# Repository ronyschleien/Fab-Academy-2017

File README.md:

# Fab-Academy-2017
All the files of my exercises

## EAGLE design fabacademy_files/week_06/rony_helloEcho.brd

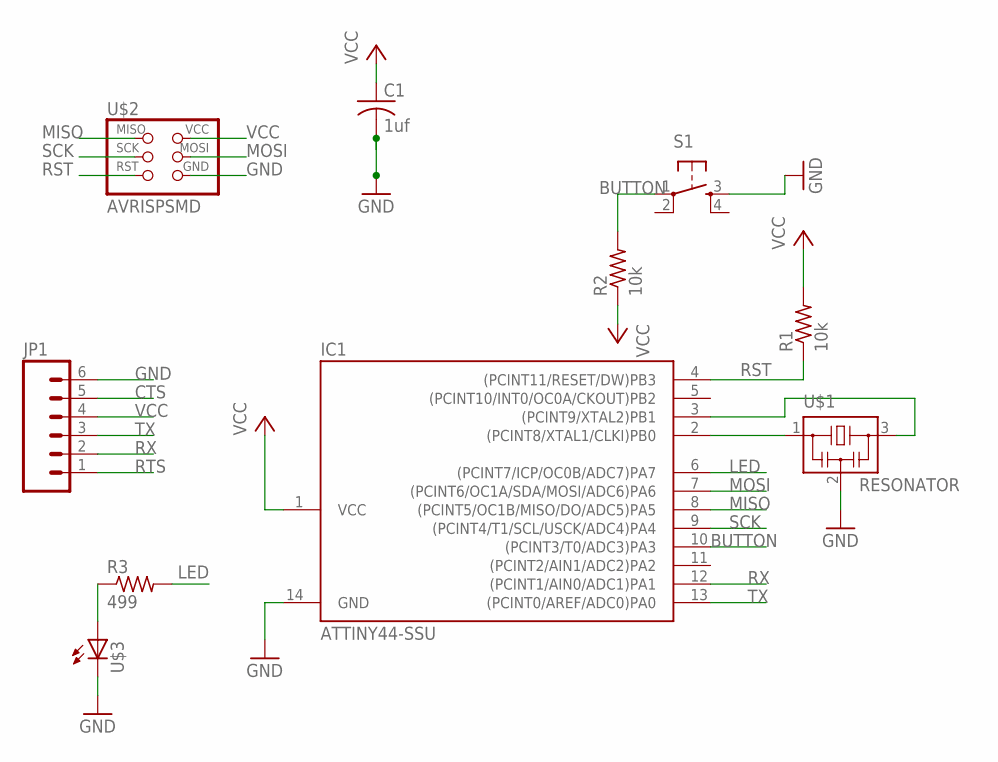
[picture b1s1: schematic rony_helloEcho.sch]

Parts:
C1: 1uf; C1206
IC1: ATTINY44-SSU; SOIC14
JP1: M06SMD; 1X06-SMD
R1, R2: 10k; R1206
R3: 499; R1206FAB
S1: 6MM_SWITCH6MM_SWITCH; 6MM_SWITCH
U$1: RESONATOR; EFOBM
U$2: AVRISPSMD; 2X03SMD
U$3: LED1206; 1206

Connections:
BUTTON: IC1.10 ((PCINT3/T0/ADC3)PA3), R2.2, S1.1
CTS: JP1.5
GND: C1.2, IC1.14 (GND), JP1.6, S1.3 (S), U$1.2, U$2.6 (GND), U$3.2 (C)
LED: IC1.6 ((PCINT7/ICP/OC0B/ADC7)PA7), R3.2
MISO: IC1.8 ((PCINT5/OC1B/MISO/DO/ADC5)PA5), U$2.1 (MISO)
MOSI: IC1.7 ((PCINT6/OC1A/SDA/MOSI/ADC6)PA6), U$2.4 (MOSI)
unnamed: IC1.2 ((PCINT8/XTAL1/CLKI)PB0), U$1.1
unnamed: IC1.3 ((PCINT9/XTAL2)PB1), U$1.3
unnamed: R3.1, U$3.1 (A)
RST: IC1.4 ((PCINT11/RESET/DW)PB3), R1.1, U$2.5 (RST)
RTS: JP1.1
RX: IC1.12 ((PCINT1/AIN0/ADC1)PA1), JP1.2
SCK: IC1.9 ((PCINT4/T1/SCL/USCK/ADC4)PA4), U$2.3 (SCK)
TX: IC1.13 ((PCINT0/AREF/ADC0)PA0), JP1.3
VCC: C1.1, IC1.1 (VCC), JP1.4, R1.2, R2.1, U$2.2 (VCC)

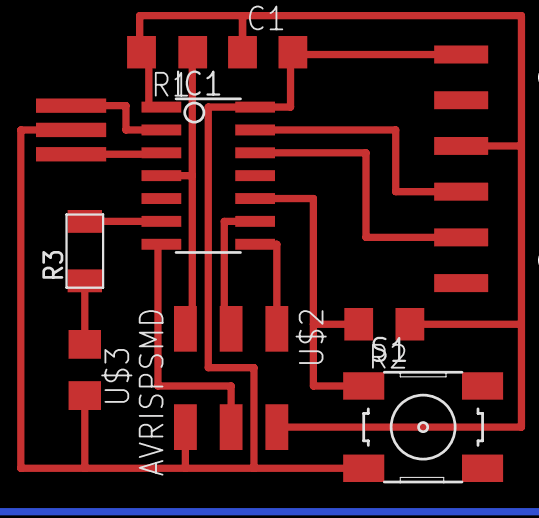
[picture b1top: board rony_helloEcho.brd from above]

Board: 1 copper layer, 10 parts (0 on the bottom side), 13 nets.

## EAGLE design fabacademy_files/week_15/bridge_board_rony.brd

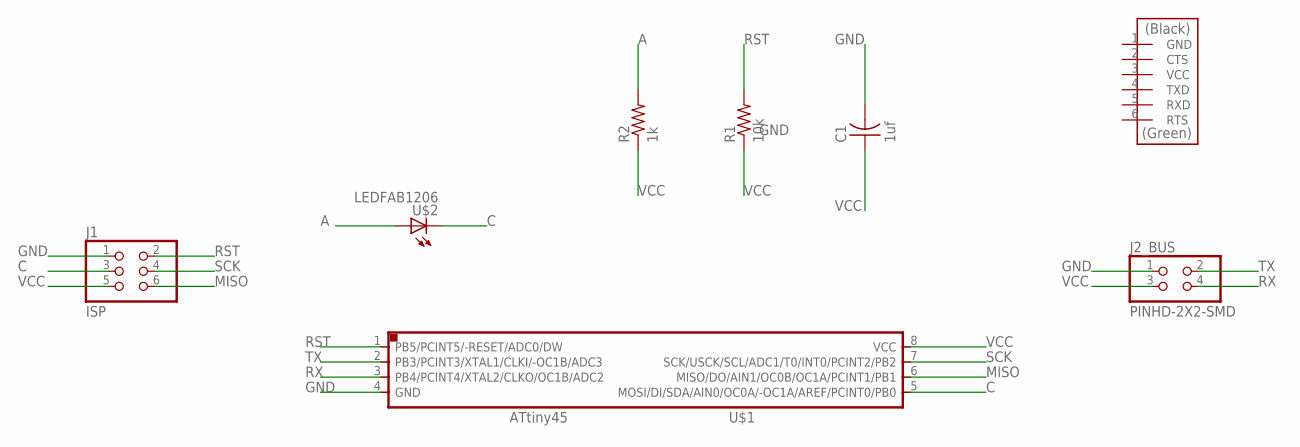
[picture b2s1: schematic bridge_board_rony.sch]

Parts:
C1: 1uf; C1206FAB
J1: ISP; 2X03SMD
J2_BUS: PINHD-2X2-SMD; 2X02SMD
R1: 10k; R1206FAB
R2: 1k; R1206FAB
U$1: ATTINY45SI; SOIC8
U$2: LEDFAB1206; LED1206FAB
U$3: FTDI-SMD-HEADER; 1X06SMD

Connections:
A: R2.2, U$2.1 (A)
C: J1.3, U$1.5 (MOSI/DI/SDA/AIN0/OC0A/-OC1A/AREF/PCINT0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), U$2.2 (C)
GND: C1.2, J1.1, J2_BUS.1, U$1.4 (GND)
MISO: J1.6, U$1.6 (MISO/DO/AIN1/OC0B/OC1A/PCINT1/PB1)
RST: J1.2, R1.2, U$1.1 (PB5/PCINT5/-RESET/ADC0/DW)
RX: J2_BUS.4, U$1.3 (PB4/PCINT4/XTAL2/CLKO/OC1B/ADC2)
SCK: J1.4, U$1.7 (SCK/USCK/SCL/ADC1/T0/INT0/PCINT2/PB2)
TX: J2_BUS.2, U$1.2 (PB3/PCINT3/XTAL1/CLKI/-OC1B/ADC3)
VCC: C1.1, J1.5, J2_BUS.3, R1.1, R2.1, U$1.8 (VCC)

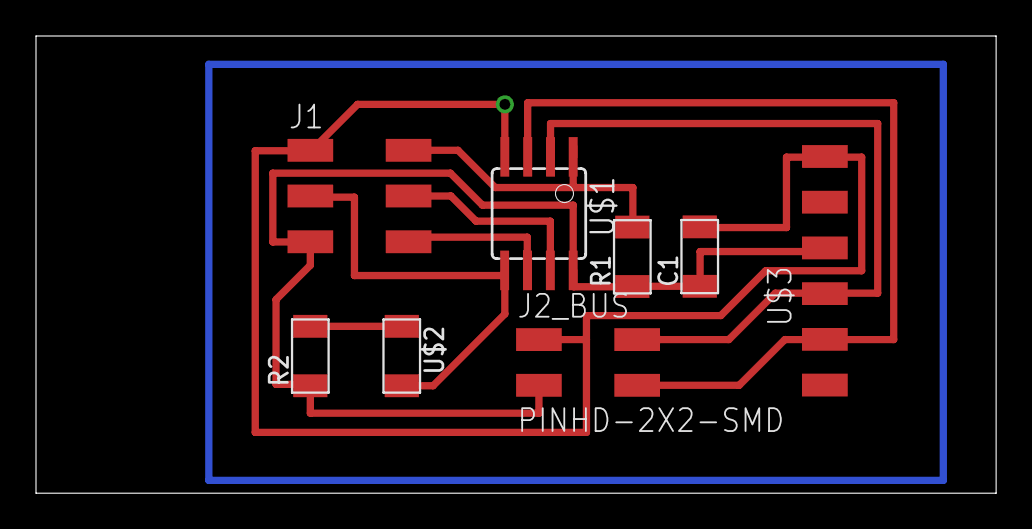
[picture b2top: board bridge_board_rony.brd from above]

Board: 2 copper layers, 53.3 x 25.4 mm, 8 parts (0 on the bottom side), 9 nets.

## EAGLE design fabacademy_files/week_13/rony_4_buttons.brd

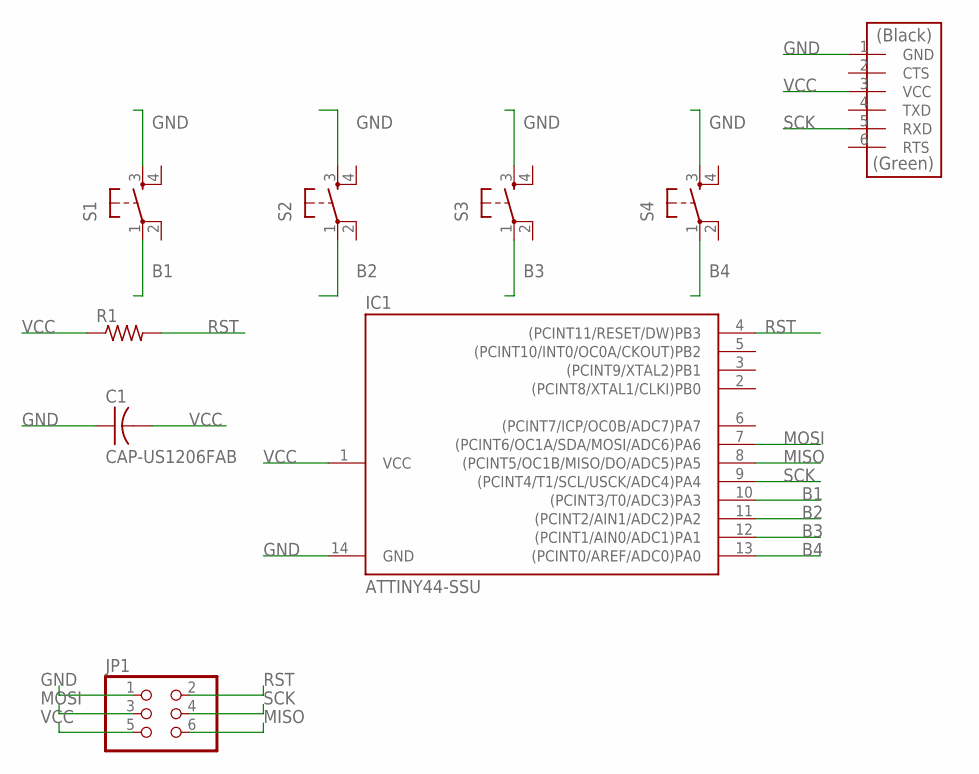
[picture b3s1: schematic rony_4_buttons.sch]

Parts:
C1: CAP-US1206FAB; C1206FAB
IC1: ATTINY44-SSU; SOIC14
JP1: PINHD-2X3-SMD; 2X03SMD
R1: RES-US1206FAB; R1206FAB
S1, S2, S3, S4: 6MM_SWITCH6MM_SWITCH; 6MM_SWITCH
U$1: FTDI-SMD-HEADER; 1X06SMD

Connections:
B1: IC1.10 ((PCINT3/T0/ADC3)PA3), S1.1
B2: IC1.11 ((PCINT2/AIN1/ADC2)PA2), S2.1
B3: IC1.12 ((PCINT1/AIN0/ADC1)PA1), S3.1
B4: IC1.13 ((PCINT0/AREF/ADC0)PA0), S4.1
GND: C1.1, IC1.14 (GND), JP1.1, S1.3 (S), S2.3 (S), S3.3 (S), S4.3 (S), U$1.1 (GND)
MISO: IC1.8 ((PCINT5/OC1B/MISO/DO/ADC5)PA5), JP1.6
MOSI: IC1.7 ((PCINT6/OC1A/SDA/MOSI/ADC6)PA6), JP1.3
RST: IC1.4 ((PCINT11/RESET/DW)PB3), JP1.2, R1.2
SCK: IC1.9 ((PCINT4/T1/SCL/USCK/ADC4)PA4), JP1.4, U$1.5 (RXD)
VCC: C1.2, IC1.1 (VCC), JP1.5, R1.1, U$1.3 (VCC)

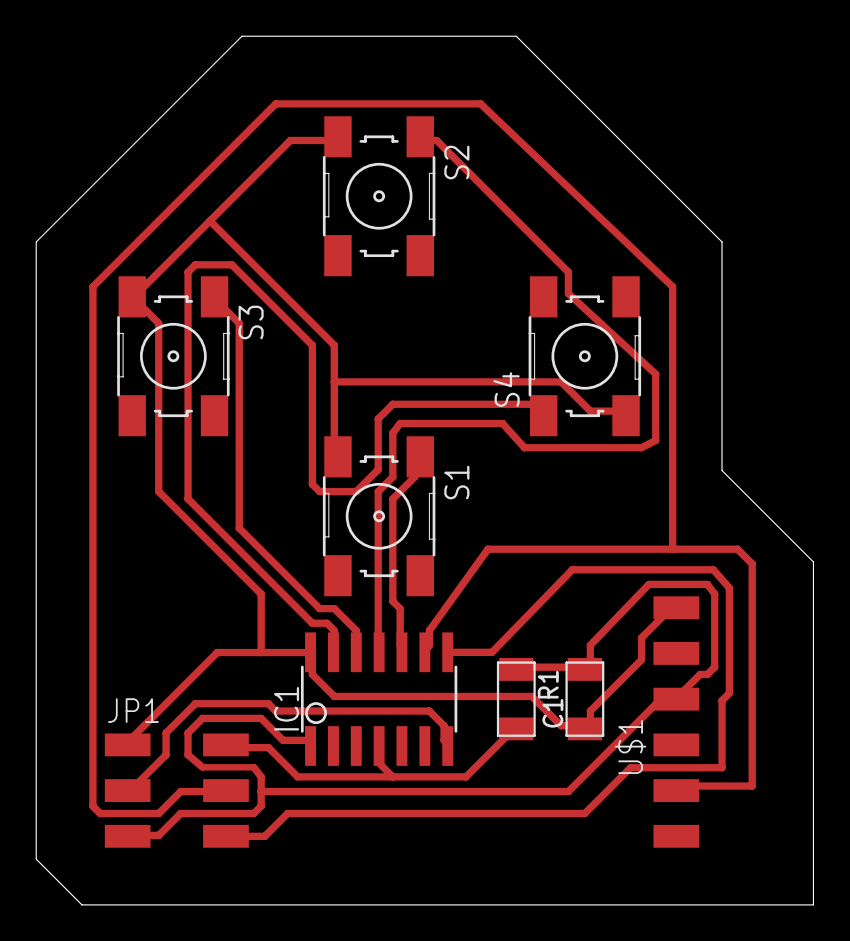
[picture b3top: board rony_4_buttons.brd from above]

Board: 2 copper layers, 43.2 x 48.3 mm, 9 parts (0 on the bottom side), 10 nets.

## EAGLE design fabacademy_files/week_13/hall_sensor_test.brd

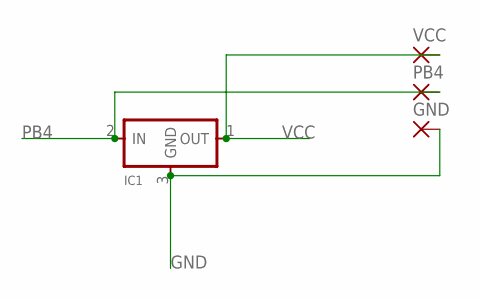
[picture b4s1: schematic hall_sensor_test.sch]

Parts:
GND: SMD2; SMD1,27-2,54
IC1: REGULATORSOT23; SOT23
PB4: SMD2; SMD1,27-2,54
VCC: SMD2; SMD1,27-2,54

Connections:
GND: GND.1, IC1.3 (GND)
PB4: IC1.2 (IN), PB4.1
VCC: IC1.1 (OUT), VCC.1

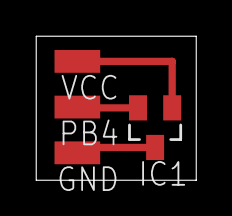
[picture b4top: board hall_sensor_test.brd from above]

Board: 2 copper layers, 8.9 x 8.0 mm, 4 parts (0 on the bottom side), 3 nets.

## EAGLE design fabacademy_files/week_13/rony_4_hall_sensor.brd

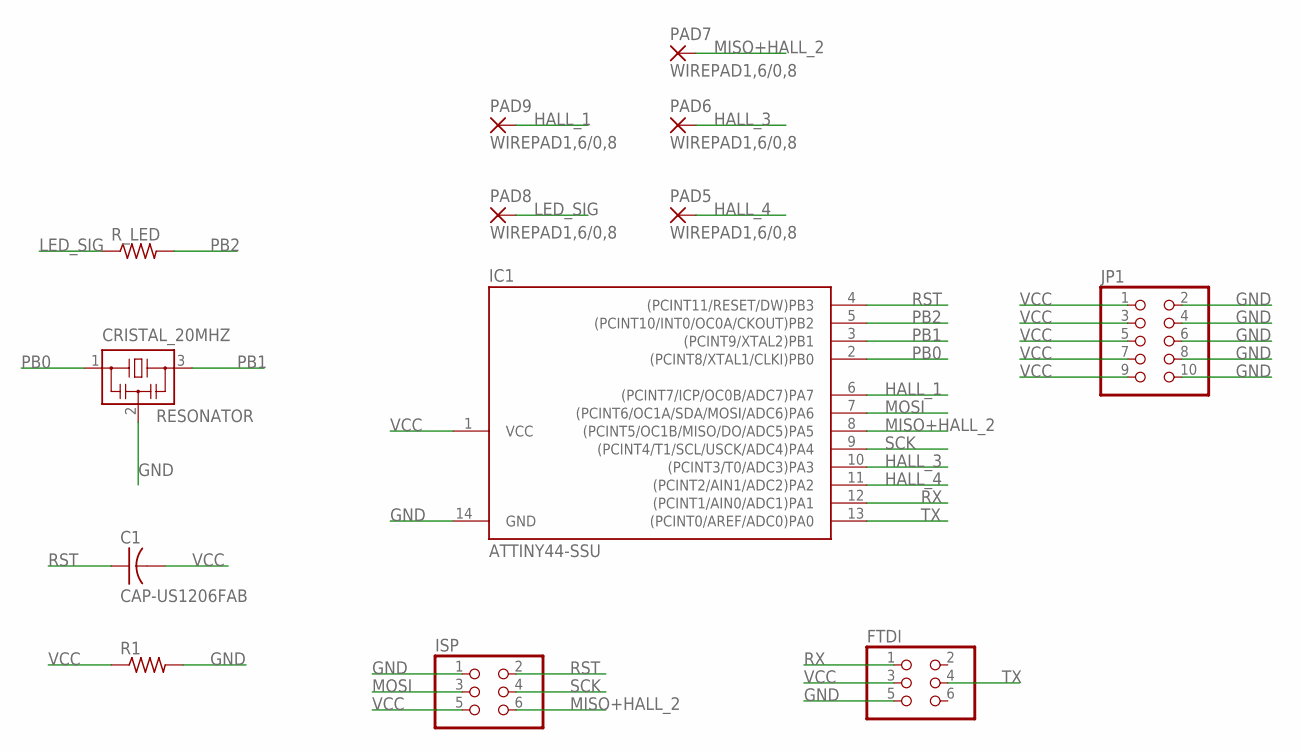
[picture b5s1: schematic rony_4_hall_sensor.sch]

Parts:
C1: CAP-US1206FAB; C1206FAB
CRISTAL_20MHZ: RESONATOR; EFOBM
FTDI: PINHD-2X3-SMD; 2X03SMD
IC1: ATTINY44-SSU; SOIC14
ISP: PINHD-2X3-SMD; 2X03SMD
JP1: PINHD-2X5; 2X05
PAD5, PAD6, PAD7, PAD8, PAD9: WIREPAD1,6/0,8; 1,6/0,8
R1: RES-US1206FAB; R1206FAB
R_LED: RES-US1206FAB; R1206FAB

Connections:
GND: CRISTAL_20MHZ.2, FTDI.5, IC1.14 (GND), ISP.1, JP1.2, JP1.4, JP1.6, JP1.8, JP1.10, R1.2
HALL_1: IC1.6 ((PCINT7/ICP/OC0B/ADC7)PA7), PAD9.1
HALL_3: IC1.10 ((PCINT3/T0/ADC3)PA3), PAD6.1
HALL_4: IC1.11 ((PCINT2/AIN1/ADC2)PA2), PAD5.1
LED_SIG: PAD8.1, R_LED.1
MISO+HALL_2: IC1.8 ((PCINT5/OC1B/MISO/DO/ADC5)PA5), ISP.6, PAD7.1
MOSI: IC1.7 ((PCINT6/OC1A/SDA/MOSI/ADC6)PA6), ISP.3
PB0: CRISTAL_20MHZ.1, IC1.2 ((PCINT8/XTAL1/CLKI)PB0)
PB1: CRISTAL_20MHZ.3, IC1.3 ((PCINT9/XTAL2)PB1)
PB2: IC1.5 ((PCINT10/INT0/OC0A/CKOUT)PB2), R_LED.2
RST: C1.1, IC1.4 ((PCINT11/RESET/DW)PB3), ISP.2
RX: FTDI.1, IC1.12 ((PCINT1/AIN0/ADC1)PA1)
SCK: IC1.9 ((PCINT4/T1/SCL/USCK/ADC4)PA4), ISP.4
TX: FTDI.4, IC1.13 ((PCINT0/AREF/ADC0)PA0)
VCC: C1.2, FTDI.3, IC1.1 (VCC), ISP.5, JP1.1, JP1.3, JP1.5, JP1.7, JP1.9, R1.1

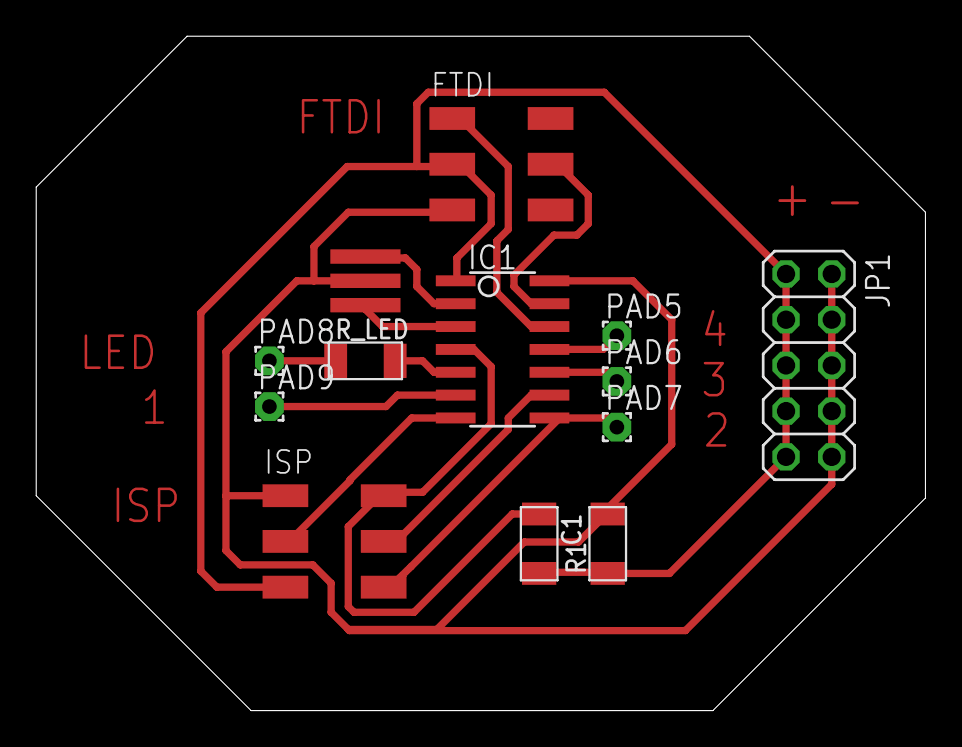
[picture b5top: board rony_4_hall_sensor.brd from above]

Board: 2 copper layers, 49.4 x 37.5 mm, 13 parts (0 on the bottom side), 15 nets.

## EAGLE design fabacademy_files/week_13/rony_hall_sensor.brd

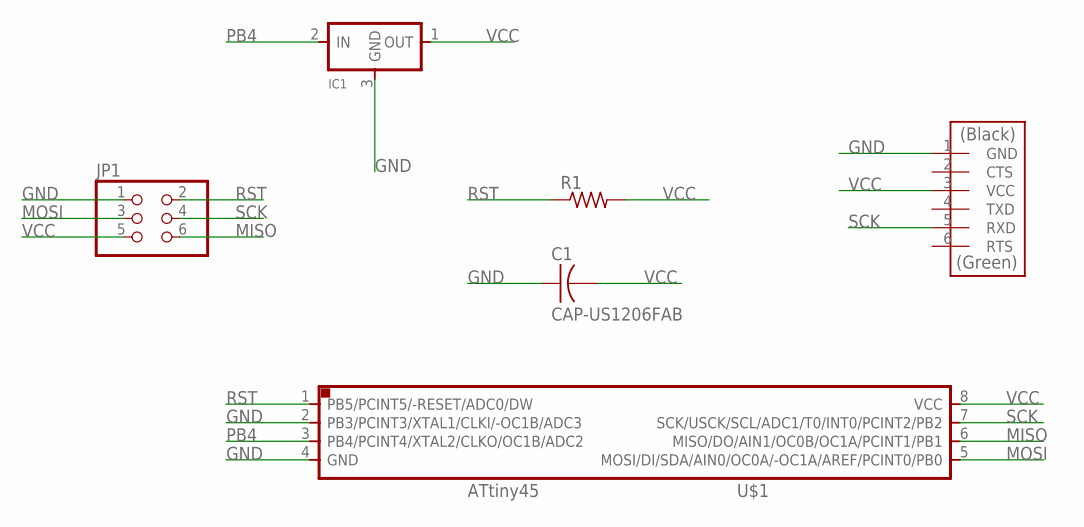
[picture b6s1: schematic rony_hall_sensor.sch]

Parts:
C1: CAP-US1206FAB; C1206FAB
IC1: REGULATORSOT23; SOT23
JP1: PINHD-2X3-SMD; 2X03SMD
R1: RES-US1206FAB; R1206FAB
U$1: ATTINY45SI; SOIC8
U$2: FTDI-SMD-HEADER; 1X06SMD

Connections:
GND: C1.1, IC1.3 (GND), JP1.1, U$1.2 (PB3/PCINT3/XTAL1/CLKI/-OC1B/ADC3), U$1.4 (GND), U$2.1 (GND)
MISO: JP1.6, U$1.6 (MISO/DO/AIN1/OC0B/OC1A/PCINT1/PB1)
MOSI: JP1.3, U$1.5 (MOSI/DI/SDA/AIN0/OC0A/-OC1A/AREF/PCINT0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)
PB4: IC1.2 (IN), U$1.3 (PB4/PCINT4/XTAL2/CLKO/OC1B/ADC2)
RST: JP1.2, R1.1, U$1.1 (PB5/PCINT5/-RESET/ADC0/DW)
SCK: JP1.4, U$1.7 (SCK/USCK/SCL/ADC1/T0/INT0/PCINT2/PB2), U$2.5 (RXD)
VCC: C1.2, IC1.1 (OUT), JP1.5, R1.2, U$1.8 (VCC), U$2.3 (VCC)

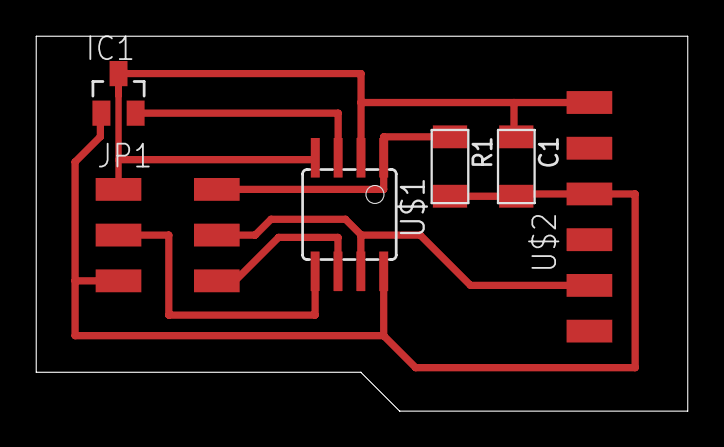
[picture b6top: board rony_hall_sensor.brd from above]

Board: 2 copper layers, 36.2 x 20.8 mm, 6 parts (0 on the bottom side), 7 nets.

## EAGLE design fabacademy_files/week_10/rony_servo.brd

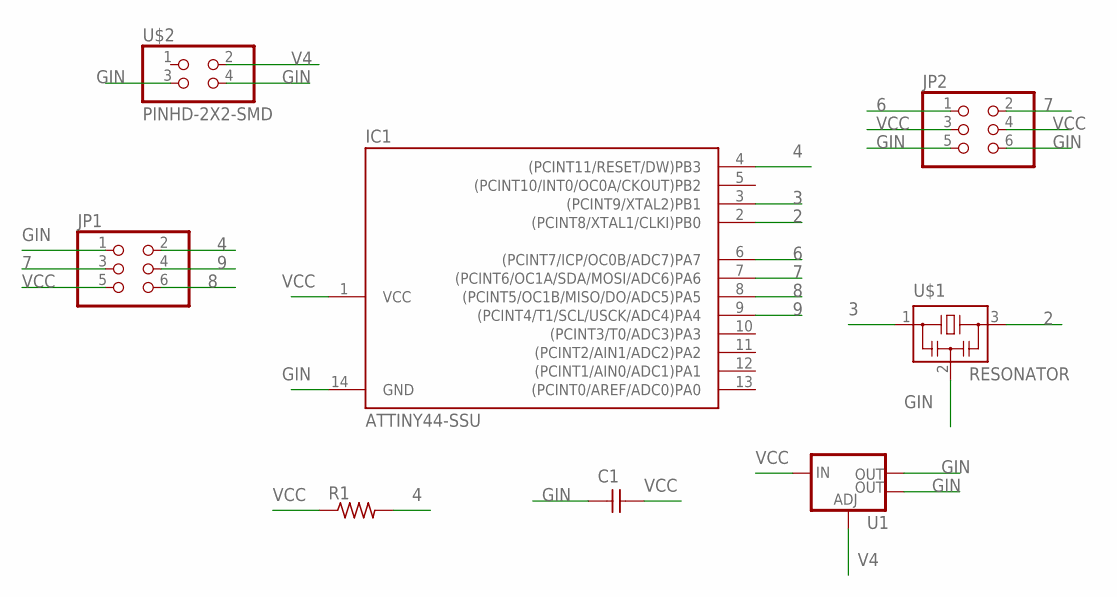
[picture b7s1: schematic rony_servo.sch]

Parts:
C1: CAP-UNPOLARIZEDFAB; C1206FAB
IC1: ATTINY44-SSU; SOIC14
JP1, JP2: PINHD-2X3-SMD; 2X03SMD
R1: RES-US1206FAB; R1206FAB
U1: V_REG_LM1117SOT223; SOT223
U$1: RESONATOR; EFOBM
U$2: PINHD-2X2-SMD; 2X02SMD

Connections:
2: IC1.2 ((PCINT8/XTAL1/CLKI)PB0), U$1.3
3: IC1.3 ((PCINT9/XTAL2)PB1), U$1.1
4: IC1.4 ((PCINT11/RESET/DW)PB3), JP1.2, R1.2
6: IC1.6 ((PCINT7/ICP/OC0B/ADC7)PA7), JP2.1
7: IC1.7 ((PCINT6/OC1A/SDA/MOSI/ADC6)PA6), JP1.3, JP2.2
8: IC1.8 ((PCINT5/OC1B/MISO/DO/ADC5)PA5), JP1.6
9: IC1.9 ((PCINT4/T1/SCL/USCK/ADC4)PA4), JP1.4
GIN: C1.1, IC1.14 (GND), JP1.1, JP2.5, JP2.6, U1.2 (OUT), U1.4 (OUT), U$1.2, U$2.3, U$2.4
V4: U1.1 (ADJ), U$2.2
VCC: C1.2, IC1.1 (VCC), JP1.5, JP2.3, JP2.4, R1.1, U1.3 (IN)

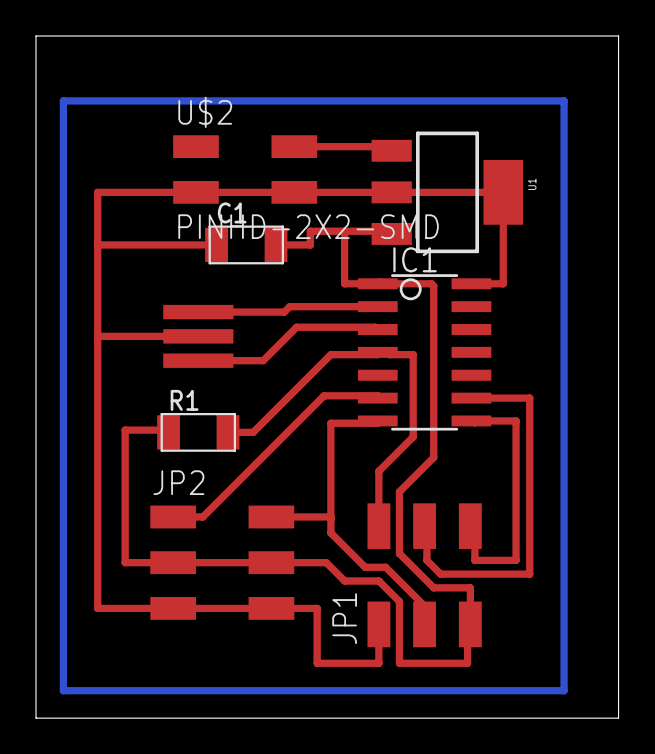
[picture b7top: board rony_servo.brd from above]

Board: 2 copper layers, 32.4 x 37.9 mm, 8 parts (0 on the bottom side), 10 nets.

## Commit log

2017-10-07 trying to create folders
2017-10-07 Create text
2017-10-07 week_03 exercises
2017-10-07 wee_05 exercises
2017-10-07 week_06 folder
2017-10-07 week_07 folder
2017-10-07 week_08 folder
2017-10-07 Create text
    week_09 folder
2017-10-07 week_09 exercise
2017-10-07 group folder
2017-10-07 week_09 group exercise
2017-10-07 week_10 folder
2017-10-07 week_11 folder
2017-10-07 week_12 folder
2017-10-07 week_12 exercises
2017-10-07 week_13 folder
2017-10-07 Deleting text file
2017-10-07 week_14 folder
2017-10-07 week_14 exercise
2017-10-07 week_15 folder
2017-10-07 week_16 folder
2017-10-07 final_project folder
2017-10-07 how to create a movie on grasshopper
2017-10-07 deleting bak file
2017-10-07 ai.file
2017-10-08 input exercise
2017-10-08 networking exercise
